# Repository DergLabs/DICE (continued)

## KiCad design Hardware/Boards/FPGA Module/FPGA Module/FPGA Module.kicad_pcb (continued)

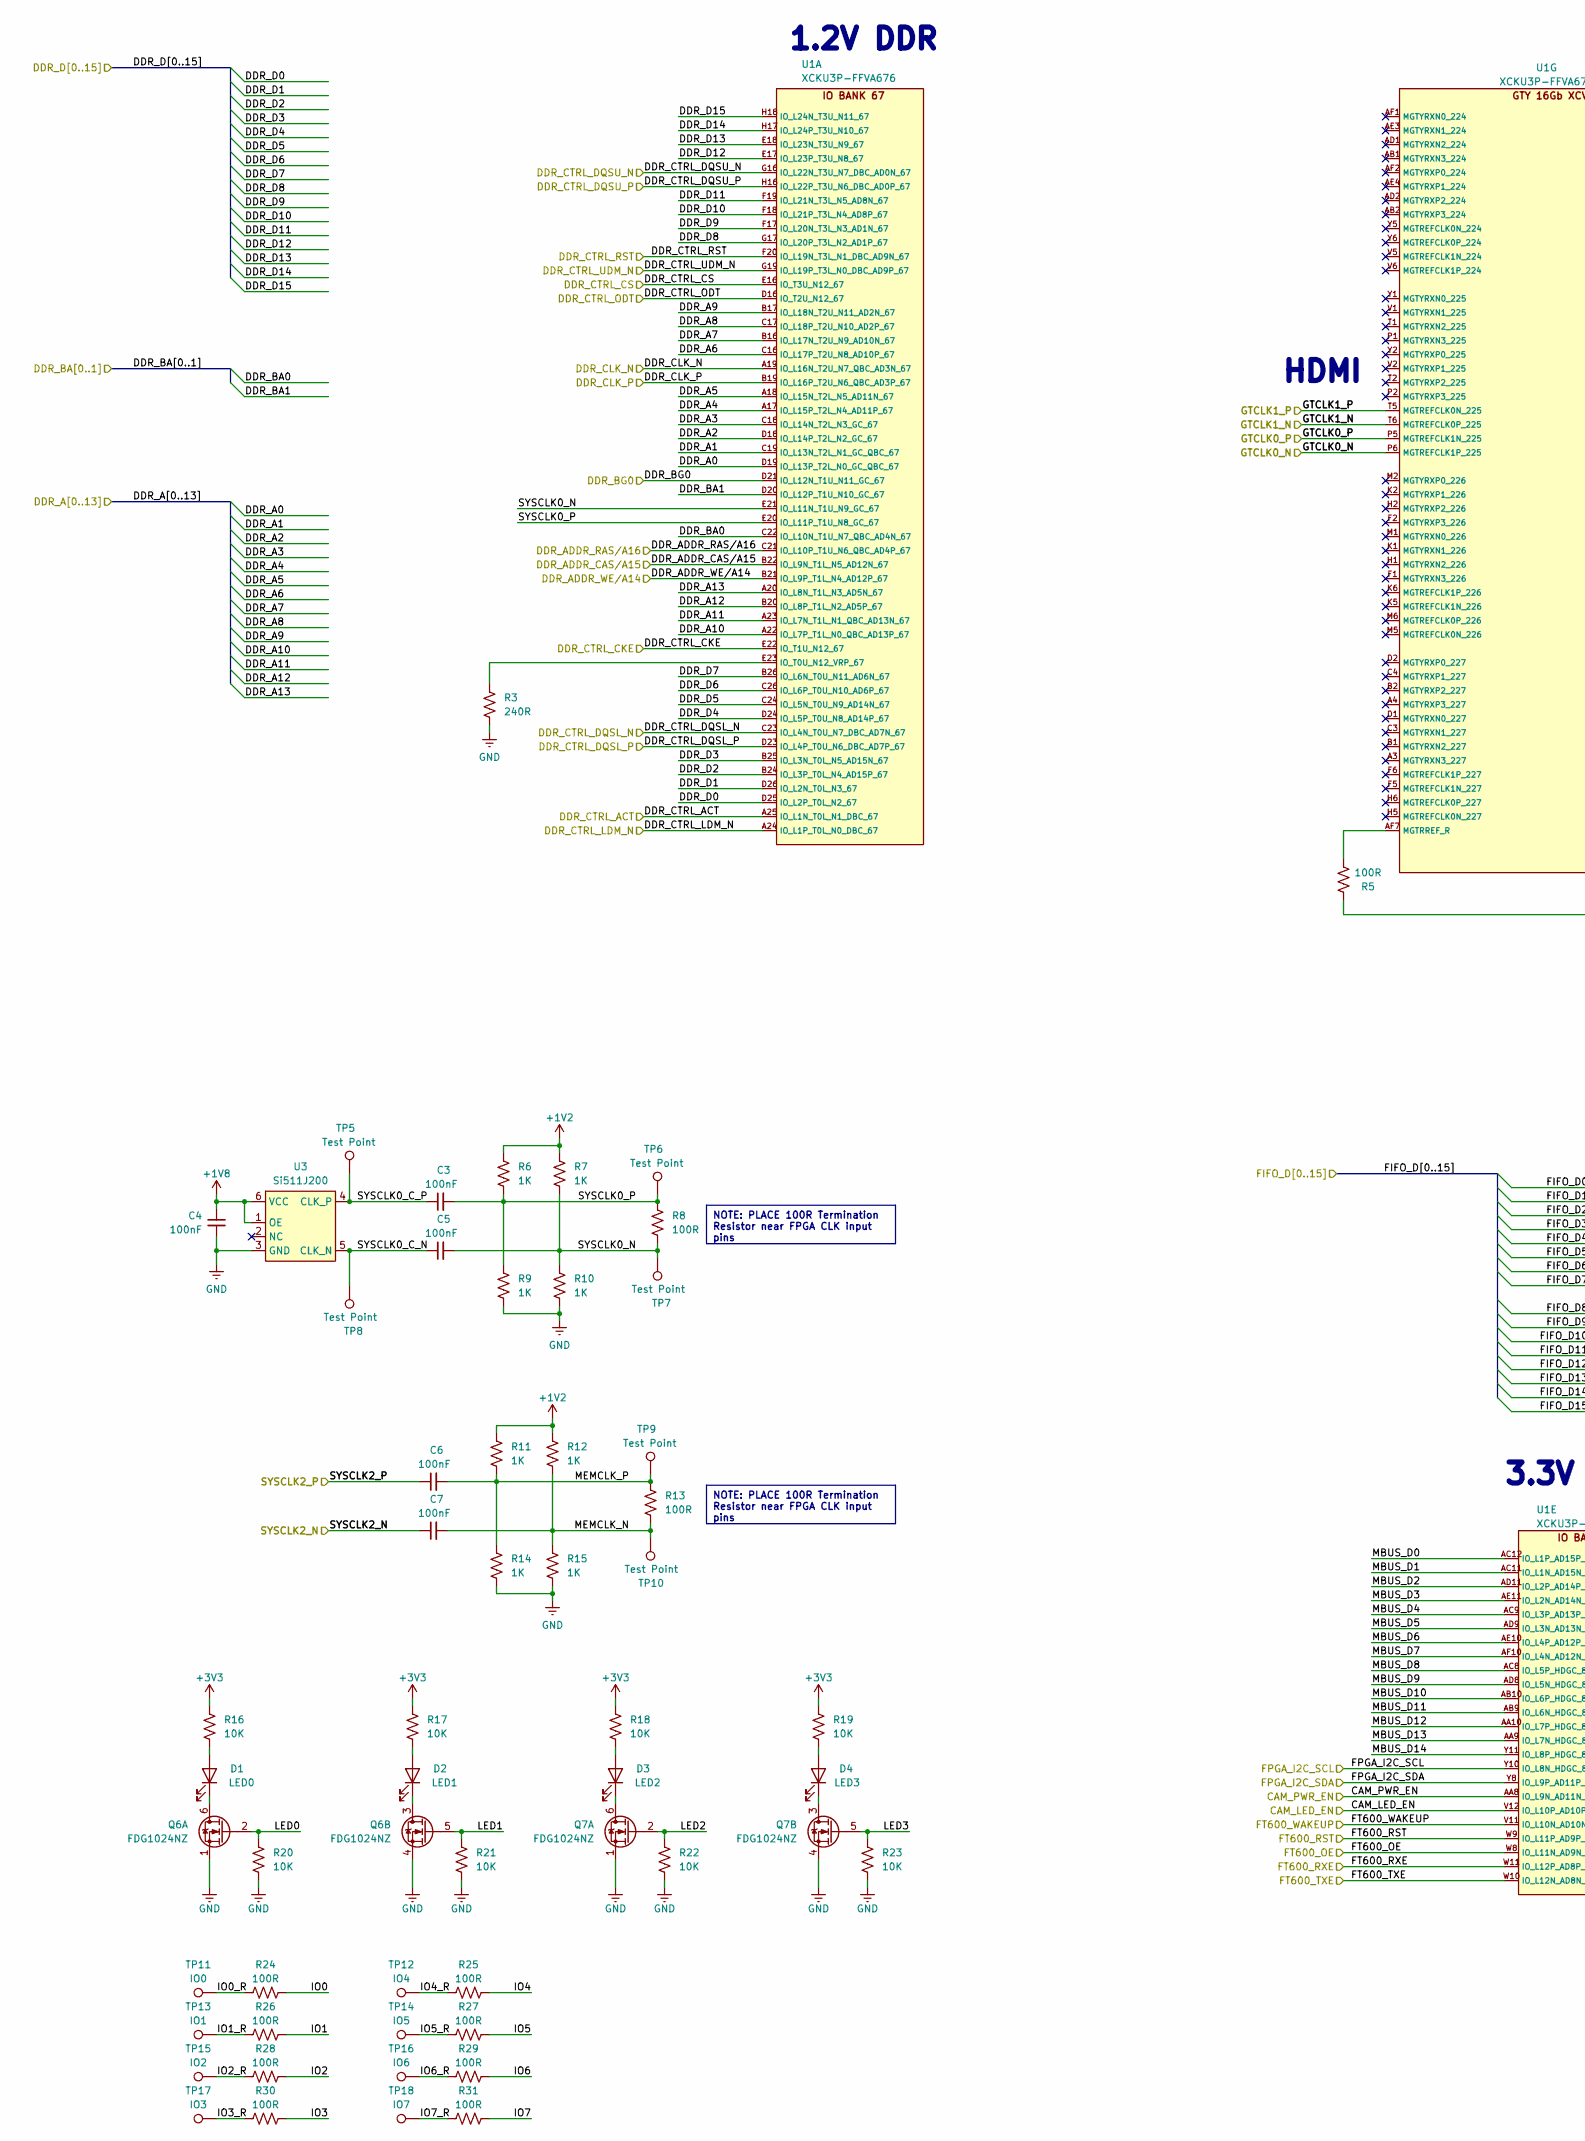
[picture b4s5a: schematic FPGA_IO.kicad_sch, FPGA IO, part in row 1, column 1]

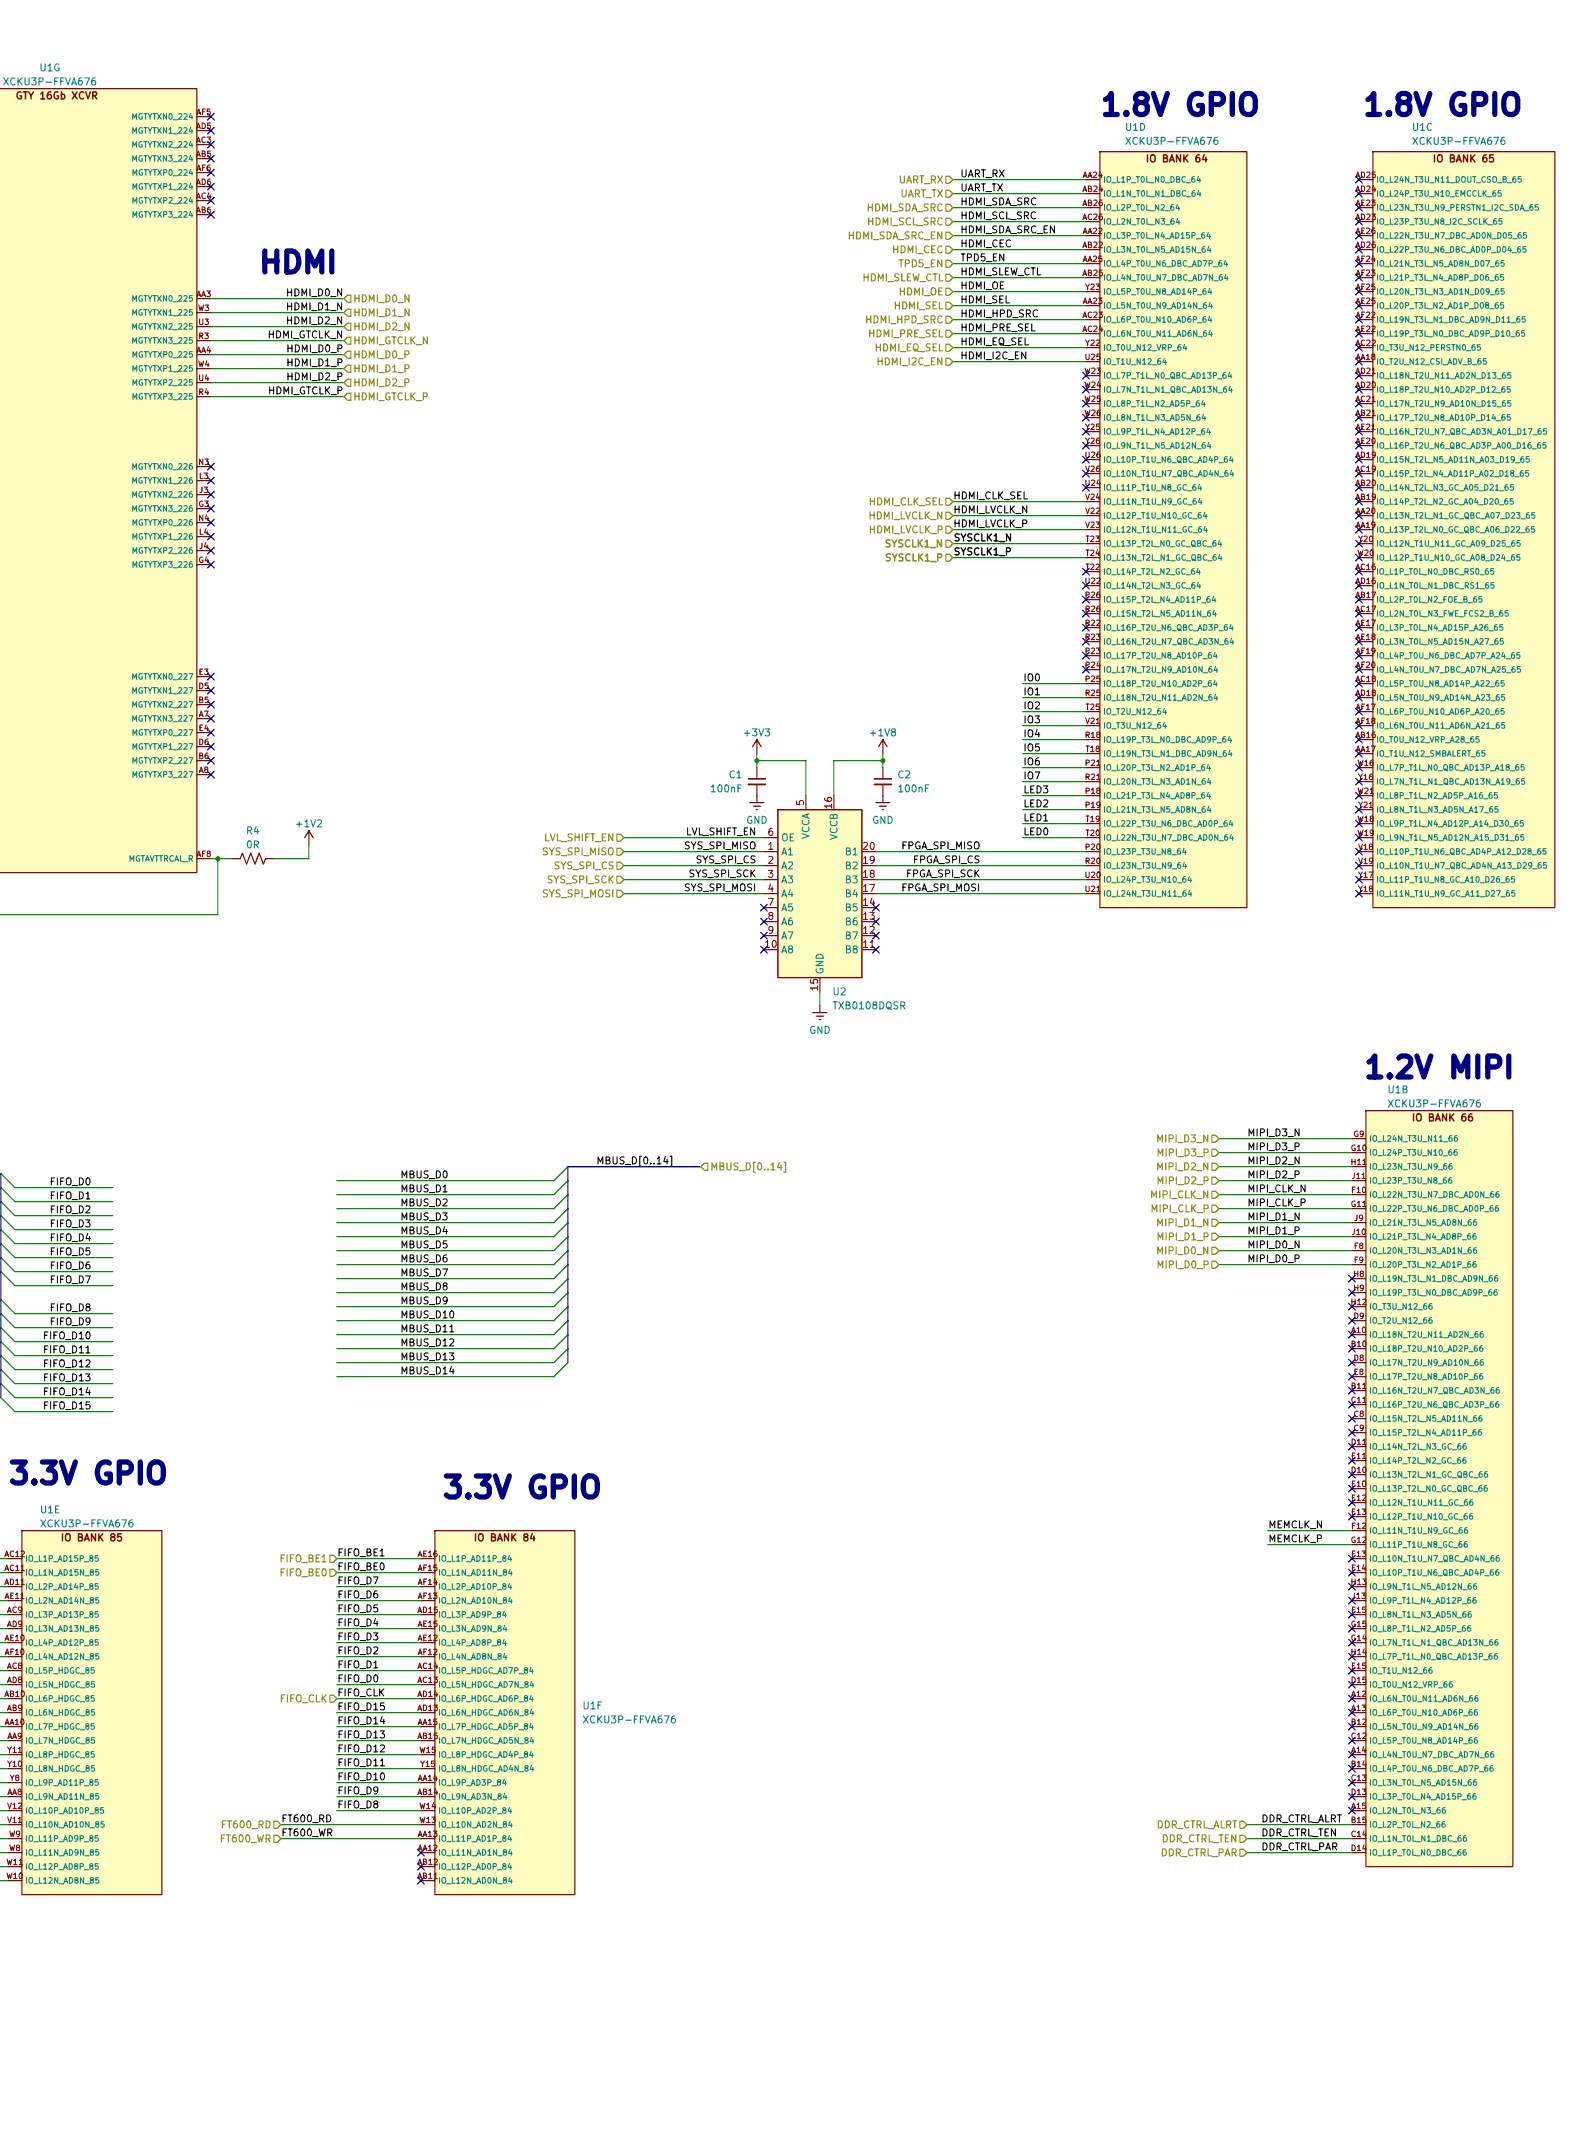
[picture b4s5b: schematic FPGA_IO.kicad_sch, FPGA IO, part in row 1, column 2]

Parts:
C1, C2, C3, C4, C5, C6, C7: 100nF; C_0201_0603Metric
D1: LED0; LED_0603_1608Metric
D2: LED1; LED_0603_1608Metric
D3: LED2; LED_0603_1608Metric
D4: LED3; LED_0603_1608Metric
Q6, Q7: FDG1024NZ; SOT-363_SC-70-6
R3: 240R; R_0201_0603Metric
R4: 0R; R_0201_0603Metric
R5, R8, R13, R24, R25, R26, R27, R28, R29, R30, R31: 100R; R_0201_0603Metric
R6, R7, R9, R10, R11, R12, R14, R15: 1K; R_0201_0603Metric
R16, R17, R18, R19, R20, R21, R22, R23: 10K; R_0201_0603Metric
TP5, TP6, TP7, TP8, TP9, TP10: Test Point; Test Point 0.75mm
TP11: IO0; Test Point 0.75mm
TP12: IO4; Test Point 0.75mm
TP13: IO1; Test Point 0.75mm
TP14: IO5; Test Point 0.75mm
TP15: IO2; Test Point 0.75mm
TP16: IO6; Test Point 0.75mm
TP17: IO3; Test Point 0.75mm
TP18: IO7; Test Point 0.75mm
U1: XCKU3P-FFVA676; BGA676
U2: TXB0108DQSR; USON-20_2x4mm_P0.4mm
U3: Si511J200; Oscillator_SMD_SiTime_SiT9121-6Pin_3.2x2.5mm

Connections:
+1V2: R4.1, R6.2, R7.2, R11.2, R12.2; also elsewhere on the board
+1V8: C2.1, C4.1, U2.16 (VCCB), U3.1 (OE), U3.6 (VCC); also elsewhere on the board
/Top/Board to Boards/CAM_LED_EN: U1.V12 (IO_L10P_AD10P_85); also elsewhere on the board
/Top/Board to Boards/CAM_PWR_EN: U1.AA8 (IO_L9N_AD11N_85); also elsewhere on the board
/Top/Board to Boards/FIFO_BE0: U1.AF15 (IO_L1N_AD11N_84); also elsewhere on the board
/Top/Board to Boards/FIFO_BE1: U1.AE16 (IO_L1P_AD11P_84); also elsewhere on the board
/Top/Board to Boards/FIFO_CLK: U1.AD14 (IO_L6P_HDGC_AD6P_84); also elsewhere on the board
/Top/Board to Boards/FIFO_D0: U1.AC13 (IO_L5N_HDGC_AD7N_84); also elsewhere on the board
/Top/Board to Boards/FIFO_D1: U1.AC14 (IO_L5P_HDGC_AD7P_84); also elsewhere on the board
/Top/Board to Boards/FIFO_D2: U1.AF12 (IO_L4N_AD8N_84); also elsewhere on the board
/Top/Board to Boards/FIFO_D3: U1.AE12 (IO_L4P_AD8P_84); also elsewhere on the board
/Top/Board to Boards/FIFO_D4: U1.AE15 (IO_L3N_AD9N_84); also elsewhere on the board
/Top/Board to Boards/FIFO_D5: U1.AD15 (IO_L3P_AD9P_84); also elsewhere on the board
/Top/Board to Boards/FIFO_D6: U1.AF13 (IO_L2N_AD10N_84); also elsewhere on the board
/Top/Board to Boards/FIFO_D7: U1.AF14 (IO_L2P_AD10P_84); also elsewhere on the board
/Top/Board to Boards/FIFO_D8: U1.W14 (IO_L10P_AD2P_84); also elsewhere on the board
/Top/Board to Boards/FIFO_D9: U1.AB14 (IO_L9N_AD3N_84); also elsewhere on the board
/Top/Board to Boards/FIFO_D10: U1.AA14 (IO_L9P_AD3P_84); also elsewhere on the board
/Top/Board to Boards/FIFO_D11: U1.Y15 (IO_L8N_HDGC_AD4N_84); also elsewhere on the board
/Top/Board to Boards/FIFO_D12: U1.W15 (IO_L8P_HDGC_AD4P_84); also elsewhere on the board
/Top/Board to Boards/FIFO_D13: U1.AB15 (IO_L7N_HDGC_AD5N_84); also elsewhere on the board
/Top/Board to Boards/FIFO_D14: U1.AA15 (IO_L7P_HDGC_AD5P_84); also elsewhere on the board
/Top/Board to Boards/FIFO_D15: U1.AD13 (IO_L6N_HDGC_AD6N_84); also elsewhere on the board
/Top/Board to Boards/FPGA_I2C_SCL: U1.Y10 (IO_L8N_HDGC_85); also elsewhere on the board
/Top/Board to Boards/FPGA_I2C_SDA: U1.Y8 (IO_L9P_AD11P_85); also elsewhere on the board
/Top/Board to Boards/FT600_OE: U1.W8 (IO_L11N_AD9N_85); also elsewhere on the board
/Top/Board to Boards/FT600_RD: U1.W13 (IO_L10N_AD2N_84); also elsewhere on the board
/Top/Board to Boards/FT600_RST: U1.W9 (IO_L11P_AD9P_85); also elsewhere on the board
/Top/Board to Boards/FT600_RXE: U1.W11 (IO_L12P_AD8P_85); also elsewhere on the board
/Top/Board to Boards/FT600_TXE: U1.W10 (IO_L12N_AD8N_85); also elsewhere on the board
/Top/Board to Boards/FT600_WAKEUP: U1.V11 (IO_L10N_AD10N_85); also elsewhere on the board
/Top/Board to Boards/FT600_WR: U1.AA13 (IO_L11P_AD1P_84); also elsewhere on the board
/Top/Board to Boards/HDMI_CEC: U1.AB22 (IO_L3N_T0L_N5_AD15N_64); also elsewhere on the board
/Top/Board to Boards/HDMI_D0_N: U1.AA3 (MGTYTXN0_225); also elsewhere on the board
/Top/Board to Boards/HDMI_D0_P: U1.AA4 (MGTYTXP0_225); also elsewhere on the board
/Top/Board to Boards/HDMI_D1_N: U1.W3 (MGTYTXN1_225); also elsewhere on the board
/Top/Board to Boards/HDMI_D1_P: U1.W4 (MGTYTXP1_225); also elsewhere on the board
/Top/Board to Boards/HDMI_D2_N: U1.U3 (MGTYTXN2_225); also elsewhere on the board
/Top/Board to Boards/HDMI_D2_P: U1.U4 (MGTYTXP2_225); also elsewhere on the board
/Top/Board to Boards/HDMI_EQ_SEL: U1.Y22 (IO_T0U_N12_VRP_64); also elsewhere on the board
/Top/Board to Boards/HDMI_HPD_SRC: U1.AC23 (IO_L6P_T0U_N10_AD6P_64); also elsewhere on the board
/Top/Board to Boards/HDMI_I2C_EN: U1.U25 (IO_T1U_N12_64); also elsewhere on the board
/Top/Board to Boards/HDMI_OE: U1.Y23 (IO_L5P_T0U_N8_AD14P_64); also elsewhere on the board
/Top/Board to Boards/HDMI_PRE_SEL: U1.AC24 (IO_L6N_T0U_N11_AD6N_64); also elsewhere on the board
/Top/Board to Boards/HDMI_SCL_SRC: U1.AC26 (IO_L2N_T0L_N3_64); also elsewhere on the board
/Top/Board to Boards/HDMI_SDA_SRC: U1.AB26 (IO_L2P_T0L_N2_64); also elsewhere on the board
/Top/Board to Boards/HDMI_SDA_SRC_EN: U1.AA22 (IO_L3P_T0L_N4_AD15P_64); also elsewhere on the board
/Top/Board to Boards/HDMI_SEL: U1.AA23 (IO_L5N_T0U_N9_AD14N_64); also elsewhere on the board
/Top/Board to Boards/HDMI_SLEW_CTL: U1.AB25 (IO_L4N_T0U_N7_DBC_AD7N_64); also elsewhere on the board
/Top/Board to Boards/MBUS_D0: U1.AC12 (IO_L1P_AD15P_85); also elsewhere on the board
/Top/Board to Boards/MBUS_D1: U1.AC11 (IO_L1N_AD15N_85); also elsewhere on the board
/Top/Board to Boards/MBUS_D2: U1.AD11 (IO_L2P_AD14P_85); also elsewhere on the board
/Top/Board to Boards/MBUS_D3: U1.AE11 (IO_L2N_AD14N_85); also elsewhere on the board
/Top/Board to Boards/MBUS_D4: U1.AC9 (IO_L3P_AD13P_85); also elsewhere on the board
/Top/Board to Boards/MBUS_D5: U1.AD9 (IO_L3N_AD13N_85); also elsewhere on the board
/Top/Board to Boards/MBUS_D6: U1.AE10 (IO_L4P_AD12P_85); also elsewhere on the board
/Top/Board to Boards/MBUS_D7: U1.AF10 (IO_L4N_AD12N_85); also elsewhere on the board
/Top/Board to Boards/MBUS_D8: U1.AC8 (IO_L5P_HDGC_85); also elsewhere on the board
/Top/Board to Boards/MBUS_D9: U1.AD8 (IO_L5N_HDGC_85); also elsewhere on the board
/Top/Board to Boards/MBUS_D10: U1.AB10 (IO_L6P_HDGC_85); also elsewhere on the board
/Top/Board to Boards/MBUS_D11: U1.AB9 (IO_L6N_HDGC_85); also elsewhere on the board
/Top/Board to Boards/MBUS_D12: U1.AA10 (IO_L7P_HDGC_85); also elsewhere on the board
/Top/Board to Boards/MBUS_D13: U1.AA9 (IO_L7N_HDGC_85); also elsewhere on the board
/Top/Board to Boards/MBUS_D14: U1.Y11 (IO_L8P_HDGC_85); also elsewhere on the board
/Top/Board to Boards/MIPI_CLK_N: U1.F10 (IO_L22N_T3U_N7_DBC_AD0N_66); also elsewhere on the board
/Top/Board to Boards/MIPI_CLK_P: U1.G11 (IO_L22P_T3U_N6_DBC_AD0P_66); also elsewhere on the board
/Top/Board to Boards/MIPI_D0_N: U1.F8 (IO_L20N_T3L_N3_AD1N_66); also elsewhere on the board
/Top/Board to Boards/MIPI_D0_P: U1.F9 (IO_L20P_T3L_N2_AD1P_66); also elsewhere on the board
/Top/Board to Boards/MIPI_D1_N: U1.J9 (IO_L21N_T3L_N5_AD8N_66); also elsewhere on the board
/Top/Board to Boards/MIPI_D1_P: U1.J10 (IO_L21P_T3L_N4_AD8P_66); also elsewhere on the board
/Top/Board to Boards/MIPI_D2_N: U1.H11 (IO_L23N_T3U_N9_66); also elsewhere on the board
/Top/Board to Boards/MIPI_D2_P: U1.J11 (IO_L23P_T3U_N8_66); also elsewhere on the board
/Top/Board to Boards/MIPI_D3_N: U1.G9 (IO_L24N_T3U_N11_66); also elsewhere on the board
/Top/Board to Boards/MIPI_D3_P: U1.G10 (IO_L24P_T3U_N10_66); also elsewhere on the board
/Top/Board to Boards/TPD5_EN: U1.AA25 (IO_L4P_T0U_N6_DBC_AD7P_64); also elsewhere on the board
/Top/Board to Boards/UART_RX: U1.AB24 (IO_L1N_T0L_N1_DBC_64); also elsewhere on the board
/Top/Board to Boards/UART_TX: U1.AA24 (IO_L1P_T0L_N0_DBC_64); also elsewhere on the board
/Top/Clock Generator/GTCLK0_N: U1.P6 (MGTREFCLK1P_225); also elsewhere on the board
/Top/Clock Generator/GTCLK0_P: U1.P5 (MGTREFCLK1N_225); also elsewhere on the board
/Top/Clock Generator/GTCLK1_N: U1.T6 (MGTREFCLK0P_225); also elsewhere on the board
/Top/Clock Generator/GTCLK1_P: U1.T5 (MGTREFCLK0N_225); also elsewhere on the board
/Top/Clock Generator/SYSCLK1_N: U1.T23 (IO_L13P_T2L_N0_GC_QBC_64); also elsewhere on the board
/Top/Clock Generator/SYSCLK1_P: U1.T24 (IO_L13N_T2L_N1_GC_QBC_64); also elsewhere on the board
/Top/Clock Generator/SYSCLK2_N: C7.1; also elsewhere on the board
/Top/Clock Generator/SYSCLK2_P: C6.1; also elsewhere on the board
/Top/DDR4/DDR_A0: U1.D19 (IO_L13P_T2L_N0_GC_QBC_67); also elsewhere on the board
/Top/DDR4/DDR_A1: U1.C19 (IO_L13N_T2L_N1_GC_QBC_67); also elsewhere on the board
/Top/DDR4/DDR_A2: U1.D18 (IO_L14P_T2L_N2_GC_67); also elsewhere on the board
/Top/DDR4/DDR_A3: U1.C18 (IO_L14N_T2L_N3_GC_67); also elsewhere on the board
/Top/DDR4/DDR_A4: U1.A17 (IO_L15P_T2L_N4_AD11P_67); also elsewhere on the board
/Top/DDR4/DDR_A5: U1.A18 (IO_L15N_T2L_N5_AD11N_67); also elsewhere on the board
/Top/DDR4/DDR_A6: U1.C16 (IO_L17P_T2U_N8_AD10P_67); also elsewhere on the board
/Top/DDR4/DDR_A7: U1.B16 (IO_L17N_T2U_N9_AD10N_67); also elsewhere on the board
/Top/DDR4/DDR_A8: U1.C17 (IO_L18P_T2U_N10_AD2P_67); also elsewhere on the board
/Top/DDR4/DDR_A9: U1.B17 (IO_L18N_T2U_N11_AD2N_67); also elsewhere on the board
/Top/DDR4/DDR_A10: U1.A22 (IO_L7P_T1L_N0_QBC_AD13P_67); also elsewhere on the board
/Top/DDR4/DDR_A11: U1.A23 (IO_L7N_T1L_N1_QBC_AD13N_67); also elsewhere on the board
/Top/DDR4/DDR_A12: U1.B20 (IO_L8P_T1L_N2_AD5P_67); also elsewhere on the board
/Top/DDR4/DDR_A13: U1.A20 (IO_L8N_T1L_N3_AD5N_67); also elsewhere on the board
/Top/DDR4/DDR_ADDR_CAS/A15: U1.B21 (IO_L9P_T1L_N4_AD12P_67); also elsewhere on the board
/Top/DDR4/DDR_ADDR_RAS/A16: U1.C21 (IO_L10P_T1U_N6_QBC_AD4P_67); also elsewhere on the board
/Top/DDR4/DDR_ADDR_WE/A14: U1.B22 (IO_L9N_T1L_N5_AD12N_67); also elsewhere on the board
/Top/DDR4/DDR_BA0: U1.C22 (IO_L10N_T1U_N7_QBC_AD4N_67); also elsewhere on the board
/Top/DDR4/DDR_BA1: U1.D20 (IO_L12P_T1U_N10_GC_67); also elsewhere on the board
/Top/DDR4/DDR_BG0: U1.D21 (IO_L12N_T1U_N11_GC_67); also elsewhere on the board
/Top/DDR4/DDR_CLK_N: U1.A19 (IO_L16N_T2U_N7_QBC_AD3N_67); also elsewhere on the board
/Top/DDR4/DDR_CLK_P: U1.B19 (IO_L16P_T2U_N6_QBC_AD3P_67); also elsewhere on the board
/Top/DDR4/DDR_CTRL_ACT: U1.A25 (IO_L1N_T0L_N1_DBC_67); also elsewhere on the board
/Top/DDR4/DDR_CTRL_ALRT: U1.B15 (IO_L2P_T0L_N2_66); also elsewhere on the board
/Top/DDR4/DDR_CTRL_CKE: U1.E22 (IO_T1U_N12_67); also elsewhere on the board
/Top/DDR4/DDR_CTRL_CS: U1.E16 (IO_T3U_N12_67); also elsewhere on the board
/Top/DDR4/DDR_CTRL_DQSL_N: U1.C23 (IO_L4N_T0U_N7_DBC_AD7N_67); also elsewhere on the board
/Top/DDR4/DDR_CTRL_DQSL_P: U1.D23 (IO_L4P_T0U_N6_DBC_AD7P_67); also elsewhere on the board
/Top/DDR4/DDR_CTRL_DQSU_N: U1.G16 (IO_L22N_T3U_N7_DBC_AD0N_67); also elsewhere on the board
/Top/DDR4/DDR_CTRL_DQSU_P: U1.H16 (IO_L22P_T3U_N6_DBC_AD0P_67); also elsewhere on the board
/Top/DDR4/DDR_CTRL_LDM_N: U1.A24 (IO_L1P_T0L_N0_DBC_67); also elsewhere on the board
/Top/DDR4/DDR_CTRL_ODT: U1.D16 (IO_T2U_N12_67); also elsewhere on the board
/Top/DDR4/DDR_CTRL_PAR: U1.D14 (IO_L1P_T0L_N0_DBC_66); also elsewhere on the board
/Top/DDR4/DDR_CTRL_RST: U1.F20 (IO_L19N_T3L_N1_DBC_AD9N_67); also elsewhere on the board
/Top/DDR4/DDR_CTRL_TEN: U1.C14 (IO_L1N_T0L_N1_DBC_66); also elsewhere on the board
/Top/DDR4/DDR_CTRL_UDM_N: U1.G19 (IO_L19P_T3L_N0_DBC_AD9P_67); also elsewhere on the board
/Top/DDR4/DDR_D0: U1.D25 (IO_L2P_T0L_N2_67); also elsewhere on the board
/Top/DDR4/DDR_D1: U1.D26 (IO_L2N_T0L_N3_67); also elsewhere on the board
/Top/DDR4/DDR_D2: U1.B24 (IO_L3P_T0L_N4_AD15P_67); also elsewhere on the board
/Top/DDR4/DDR_D3: U1.B25 (IO_L3N_T0L_N5_AD15N_67); also elsewhere on the board
/Top/DDR4/DDR_D4: U1.D24 (IO_L5P_T0U_N8_AD14P_67); also elsewhere on the board
/Top/DDR4/DDR_D5: U1.C24 (IO_L5N_T0U_N9_AD14N_67); also elsewhere on the board
/Top/DDR4/DDR_D6: U1.C26 (IO_L6P_T0U_N10_AD6P_67); also elsewhere on the board
/Top/DDR4/DDR_D7: U1.B26 (IO_L6N_T0U_N11_AD6N_67); also elsewhere on the board
/Top/DDR4/DDR_D8: U1.G17 (IO_L20P_T3L_N2_AD1P_67); also elsewhere on the board
/Top/DDR4/DDR_D9: U1.F17 (IO_L20N_T3L_N3_AD1N_67); also elsewhere on the board
/Top/DDR4/DDR_D10: U1.F18 (IO_L21P_T3L_N4_AD8P_67); also elsewhere on the board
/Top/DDR4/DDR_D11: U1.F19 (IO_L21N_T3L_N5_AD8N_67); also elsewhere on the board
/Top/DDR4/DDR_D12: U1.E17 (IO_L23P_T3U_N8_67); also elsewhere on the board
/Top/DDR4/DDR_D13: U1.E18 (IO_L23N_T3U_N9_67); also elsewhere on the board
/Top/DDR4/DDR_D14: U1.H17 (IO_L24P_T3U_N10_67); also elsewhere on the board
/Top/DDR4/DDR_D15: U1.H18 (IO_L24N_T3U_N11_67); also elsewhere on the board
/Top/FPGA IO/FPGA_SPI_CS: U1.R20 (IO_L23N_T3U_N9_64), U2.19 (B2)
/Top/FPGA IO/FPGA_SPI_MISO: U1.P20 (IO_L23P_T3U_N8_64), U2.20 (B1)
/Top/FPGA IO/FPGA_SPI_MOSI: U1.U21 (IO_L24N_T3U_N11_64), U2.17 (B4)
/Top/FPGA IO/FPGA_SPI_SCK: U1.U20 (IO_L24P_T3U_N10_64), U2.18 (B3)
/Top/FPGA IO/HDMI_CLK_SEL: U1.V24 (IO_L11N_T1U_N9_GC_64); also elsewhere on the board
/Top/FPGA IO/HDMI_GTCLK_N: U1.R3 (MGTYTXN3_225); also elsewhere on the board
/Top/FPGA IO/HDMI_GTCLK_P: U1.R4 (MGTYTXP3_225); also elsewhere on the board
/Top/FPGA IO/HDMI_LVCLK_N: U1.V22 (IO_L12P_T1U_N10_GC_64); also elsewhere on the board
/Top/FPGA IO/HDMI_LVCLK_P: U1.V23 (IO_L12N_T1U_N11_GC_64); also elsewhere on the board
/Top/FPGA IO/IO0: R24.1, U1.P25 (IO_L18P_T2U_N10_AD2P_64)
/Top/FPGA IO/IO0_R: R24.2, TP11.1
/Top/FPGA IO/IO2: R28.1, U1.T25 (IO_T2U_N12_64)
/Top/FPGA IO/IO2_R: R28.2, TP15.1
/Top/FPGA IO/IO3: R30.1, U1.V21 (IO_T3U_N12_64)
/Top/FPGA IO/IO3_R: R30.2, TP17.1
/Top/FPGA IO/IO6: R29.1, U1.P21 (IO_L20P_T3L_N2_AD1P_64)
/Top/FPGA IO/IO6_R: R29.2, TP16.1
/Top/FPGA IO/IO7: R31.1, U1.R21 (IO_L20N_T3L_N3_AD1N_64)
/Top/FPGA IO/IO7_R: R31.2, TP18.1
/Top/FPGA IO/LED0: Q6.2 (G), R20.2, U1.T20 (IO_L22N_T3U_N7_DBC_AD0N_64)
/Top/FPGA IO/LED1: Q6.5 (G), R21.2, U1.T19 (IO_L22P_T3U_N6_DBC_AD0P_64)
/Top/FPGA IO/LED2: Q7.2 (G), R22.2, U1.P19 (IO_L21N_T3L_N5_AD8N_64)
/Top/FPGA IO/LED3: Q7.5 (G), R23.2, U1.P18 (IO_L21P_T3L_N4_AD8P_64)
/Top/FPGA IO/MEMCLK_N: C7.2, R12.1, R13.1, R15.2, TP10.1, U1.F12 (IO_L11N_T1U_N9_GC_66)
/Top/FPGA IO/MEMCLK_P: C6.2, R11.1, R13.2, R14.2, TP9.1, U1.G12 (IO_L11P_T1U_N8_GC_66)
/Top/FPGA IO/SYSCLK0_C_N: C5.1, TP8.1, U3.5 (CLK_N)
/Top/FPGA IO/SYSCLK0_C_P: C3.1, TP5.1, U3.4 (CLK_P)
/Top/FPGA IO/SYSCLK0_N: C5.2, R7.1, R8.1, R10.2, TP7.1, U1.E21 (IO_L11N_T1U_N9_GC_67)
/Top/FPGA IO/SYSCLK0_P: C3.2, R6.1, R8.2, R9.2, TP6.1, U1.E20 (IO_L11P_T1U_N8_GC_67)
/Top/LVL_SHIFT_EN: U2.6 (OE); also elsewhere on the board
/Top/SYS_SPI_CS: U2.2 (A2); also elsewhere on the board
/Top/SYS_SPI_MISO: U2.1 (A1); also elsewhere on the board
/Top/SYS_SPI_MOSI: U2.4 (A4); also elsewhere on the board
/Top/SYS_SPI_SCK: U2.3 (A3); also elsewhere on the board
unnamed: D1.2 (A), R16.1
unnamed: D1.1 (K), Q6.6 (D)
unnamed: D2.1 (K), Q6.3 (D)
unnamed: D3.2 (A), R18.1
unnamed: D3.1 (K), Q7.6 (D)
unnamed: R3.2, U1.E23 (IO_T0U_N12_VRP_67)
unnamed: R4.2, R5.1, U1.AF8 (MGTAVTTRCAL_R)
unnamed: R5.2, U1.AF7 (MGTRREF_R)

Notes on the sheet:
NOTE: PLACE 100R Termination Resistor near FPGA CLK input pins
1.8V GPIO
1.2V DDR
HDMI
3.3V GPIO
1.2V MIPI

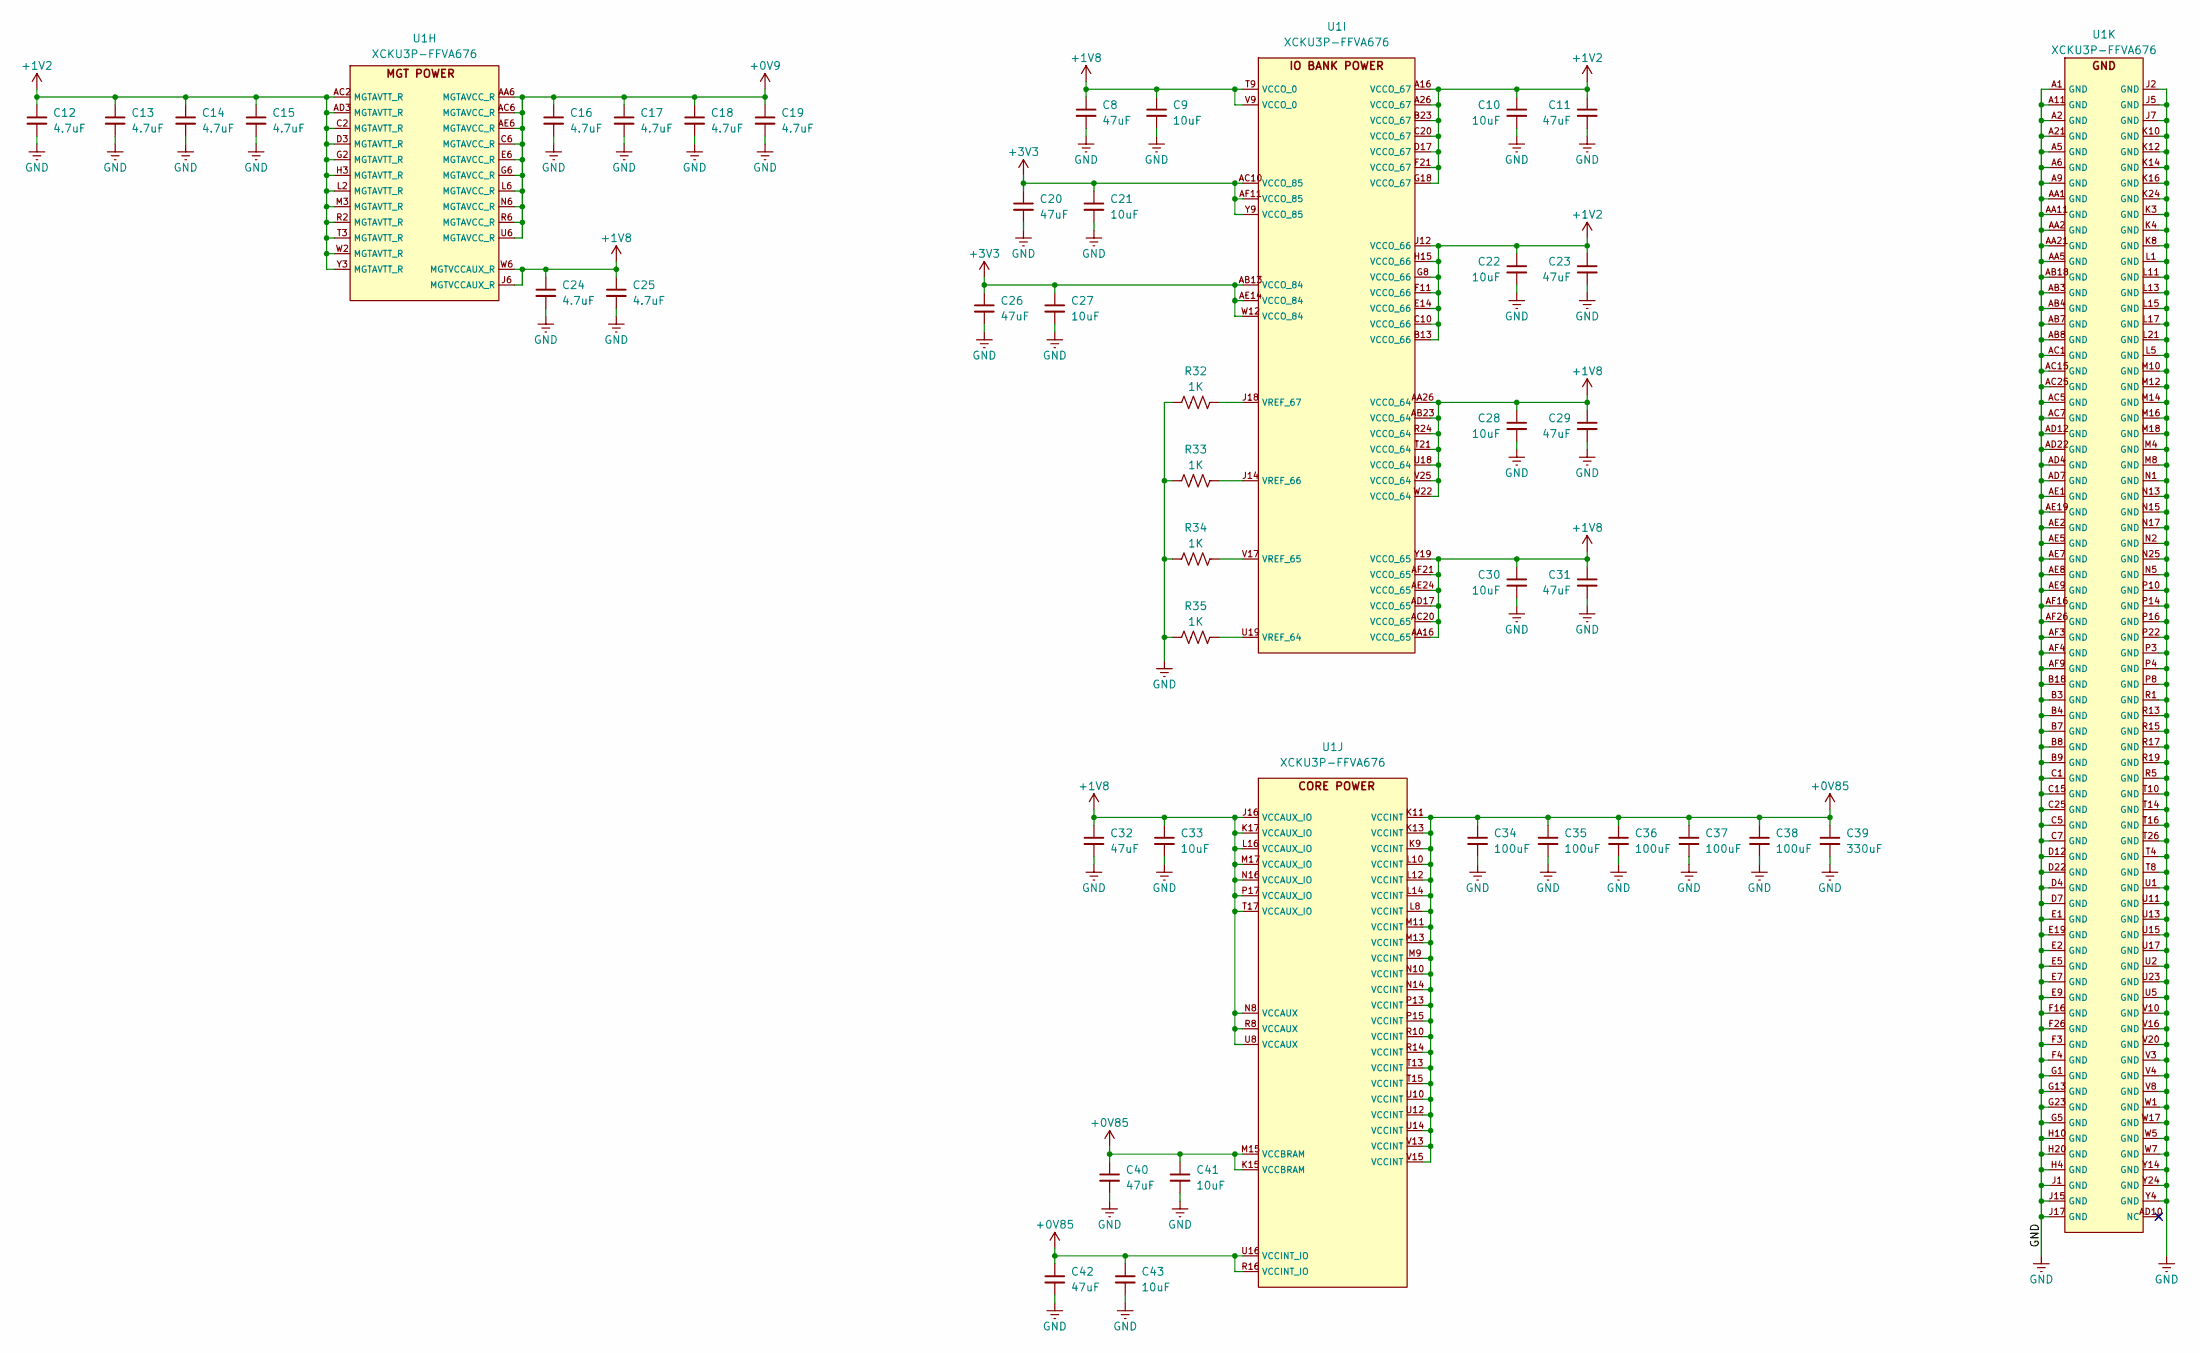
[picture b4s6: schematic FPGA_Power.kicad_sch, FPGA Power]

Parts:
C8, C11, C20, C23, C26, C29, C31, C32, C40, C42: 47uF; C_0603_1608Metric
C9, C10, C21, C22, C27, C28, C30, C33, C41, C43: 10uF; C_0402_1005Metric
C12, C13, C14, C15, C16, C17, C18, C19, C24, C25: 4.7uF; C_0402_1005Metric
C34, C35, C36, C37, C38: 100uF; C_0805_2012Metric
C39: 330uF; C_1210_3225Metric
R32, R33, R34, R35: 1K; R_0201_0603Metric
U1: XCKU3P-FFVA676; BGA676

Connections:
+0V9: C16.1, C17.1, C18.1, C19.1, U1.AA6 (MGTAVCC_R), U1.AC6 (MGTAVCC_R), U1.AE6 (MGTAVCC_R), U1.C6 (MGTAVCC_R), U1.E6 (MGTAVCC_R), U1.G6 (MGTAVCC_R), U1.L6 (MGTAVCC_R), U1.N6 (MGTAVCC_R), U1.R6 (MGTAVCC_R), U1.U6 (MGTAVCC_R); also elsewhere on the board
+0V85: C34.1, C35.1, C36.1, C37.1, C38.1, C39.1, C40.1, C41.1, C42.1, C43.1, U1.K9 (VCCINT), U1.K11 (VCCINT), U1.K13 (VCCINT), U1.K15 (VCCBRAM), U1.L8 (VCCINT), U1.L10 (VCCINT), U1.L12 (VCCINT), U1.L14 (VCCINT), U1.M9 (VCCINT), U1.M11 (VCCINT), U1.M13 (VCCINT), U1.M15 (VCCBRAM), U1.N10 (VCCINT), U1.N14 (VCCINT), U1.P13 (VCCINT), U1.P15 (VCCINT), U1.R10 (VCCINT), U1.R14 (VCCINT), U1.R16 (VCCINT_IO), U1.T13 (VCCINT), U1.T15 (VCCINT), U1.U10 (VCCINT), U1.U12 (VCCINT), U1.U14 (VCCINT), U1.U16 (VCCINT_IO), U1.V13 (VCCINT), U1.V15 (VCCINT); also elsewhere on the board
+1V2: C10.1, C11.1, C12.1, C13.1, C14.1, C15.1, C22.1, C23.1, U1.A16 (VCCO_67), U1.A26 (VCCO_67), U1.AC2 (MGTAVTT_R), U1.AD3 (MGTAVTT_R), U1.B13 (VCCO_66), U1.B23 (VCCO_67), U1.C2 (MGTAVTT_R), U1.C10 (VCCO_66), U1.C20 (VCCO_67), U1.D3 (MGTAVTT_R), U1.D17 (VCCO_67), U1.E14 (VCCO_66), U1.F11 (VCCO_66), U1.F21 (VCCO_67), U1.G2 (MGTAVTT_R), U1.G8 (VCCO_66), U1.G18 (VCCO_67), U1.H3 (MGTAVTT_R), U1.H15 (VCCO_66), U1.J12 (VCCO_66), U1.L2 (MGTAVTT_R), U1.M3 (MGTAVTT_R), U1.R2 (MGTAVTT_R), U1.T3 (MGTAVTT_R), U1.W2 (MGTAVTT_R), U1.Y3 (MGTAVTT_R); also elsewhere on the board
+1V8: C8.1, C9.1, C24.1, C25.1, C28.1, C29.1, C30.1, C31.1, C32.1, C33.1, U1.AA16 (VCCO_65), U1.AA26 (VCCO_64), U1.AB23 (VCCO_64), U1.AC20 (VCCO_65), U1.AD17 (VCCO_65), U1.AE24 (VCCO_65), U1.AF21 (VCCO_65), U1.J6 (MGTVCCAUX_R), U1.J16 (VCCAUX_IO), U1.K17 (VCCAUX_IO), U1.L16 (VCCAUX_IO), U1.M17 (VCCAUX_IO), U1.N8 (VCCAUX), U1.N16 (VCCAUX_IO), U1.P17 (VCCAUX_IO), U1.R8 (VCCAUX), U1.R24 (VCCO_64), U1.T9 (VCCO_0), U1.T17 (VCCAUX_IO), U1.T21 (VCCO_64), U1.U8 (VCCAUX), U1.U18 (VCCO_64), U1.V9 (VCCO_0), U1.V25 (VCCO_64), U1.W6 (MGTVCCAUX_R), U1.W22 (VCCO_64), U1.Y19 (VCCO_65); also elsewhere on the board
unnamed: R35.1, U1.U19 (VREF_64)
unnamed: R34.1, U1.V17 (VREF_65)
unnamed: R33.1, U1.J14 (VREF_66)
unnamed: R32.1, U1.J18 (VREF_67)

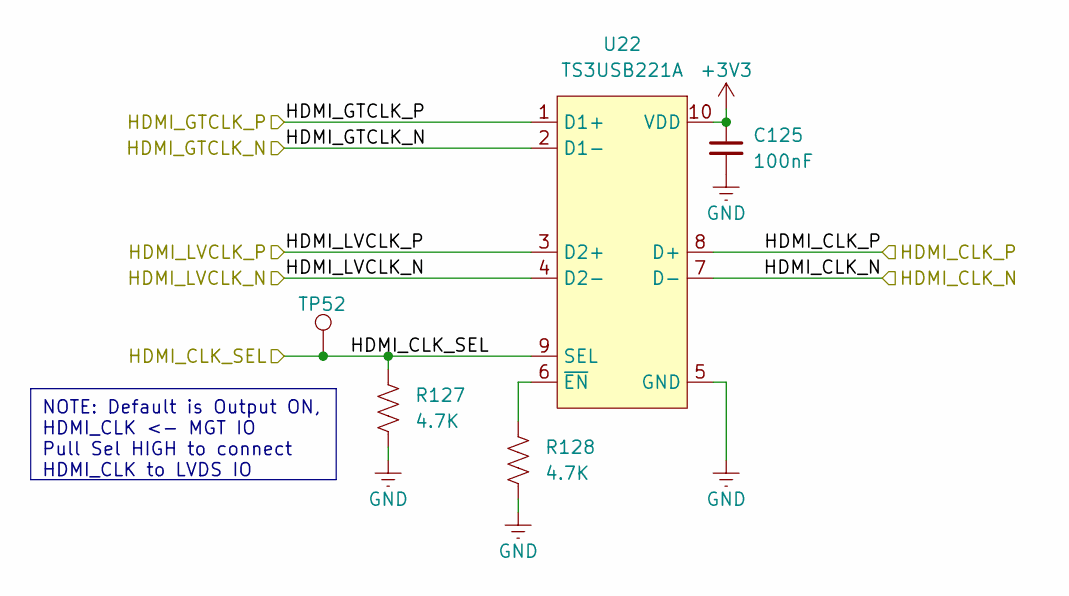
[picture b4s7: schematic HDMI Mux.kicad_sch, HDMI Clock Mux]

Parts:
C125: 100nF; C_0201_0603Metric
R127, R128: 4.7K; R_0201_0603Metric
TP52: Test Point; Test Point 0.75mm
U22: TS3USB221A; TS3USB

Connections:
/Top/Board to Boards/HDMI_CLK_N: U22.7 (D-); also elsewhere on the board
/Top/Board to Boards/HDMI_CLK_P: U22.8 (D+); also elsewhere on the board
/Top/FPGA IO/HDMI_CLK_SEL: R127.2, TP52.1, U22.9 (SEL); also elsewhere on the board
/Top/FPGA IO/HDMI_GTCLK_N: U22.2 (D1-); also elsewhere on the board
/Top/FPGA IO/HDMI_GTCLK_P: U22.1 (D1+); also elsewhere on the board
/Top/FPGA IO/HDMI_LVCLK_N: U22.4 (D2-); also elsewhere on the board
/Top/FPGA IO/HDMI_LVCLK_P: U22.3 (D2+); also elsewhere on the board
unnamed: R128.2, U22.6 (~EN)

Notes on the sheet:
NOTE: Default is Output ON, HDMI_CLK <- MGT IO Pull Sel HIGH to connect HDMI_CLK to LVDS IO
